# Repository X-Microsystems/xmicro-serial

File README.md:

# XMICRO-SERIAL

[XMICRO](https://github.com/x-microsystems/xmicro-bus) serial communications card providing two RS-232 ports and a PS/2 port.

Datasheet: [XMICRO-SERIAL](Documentation/XMICRO-SERIAL.pdf)

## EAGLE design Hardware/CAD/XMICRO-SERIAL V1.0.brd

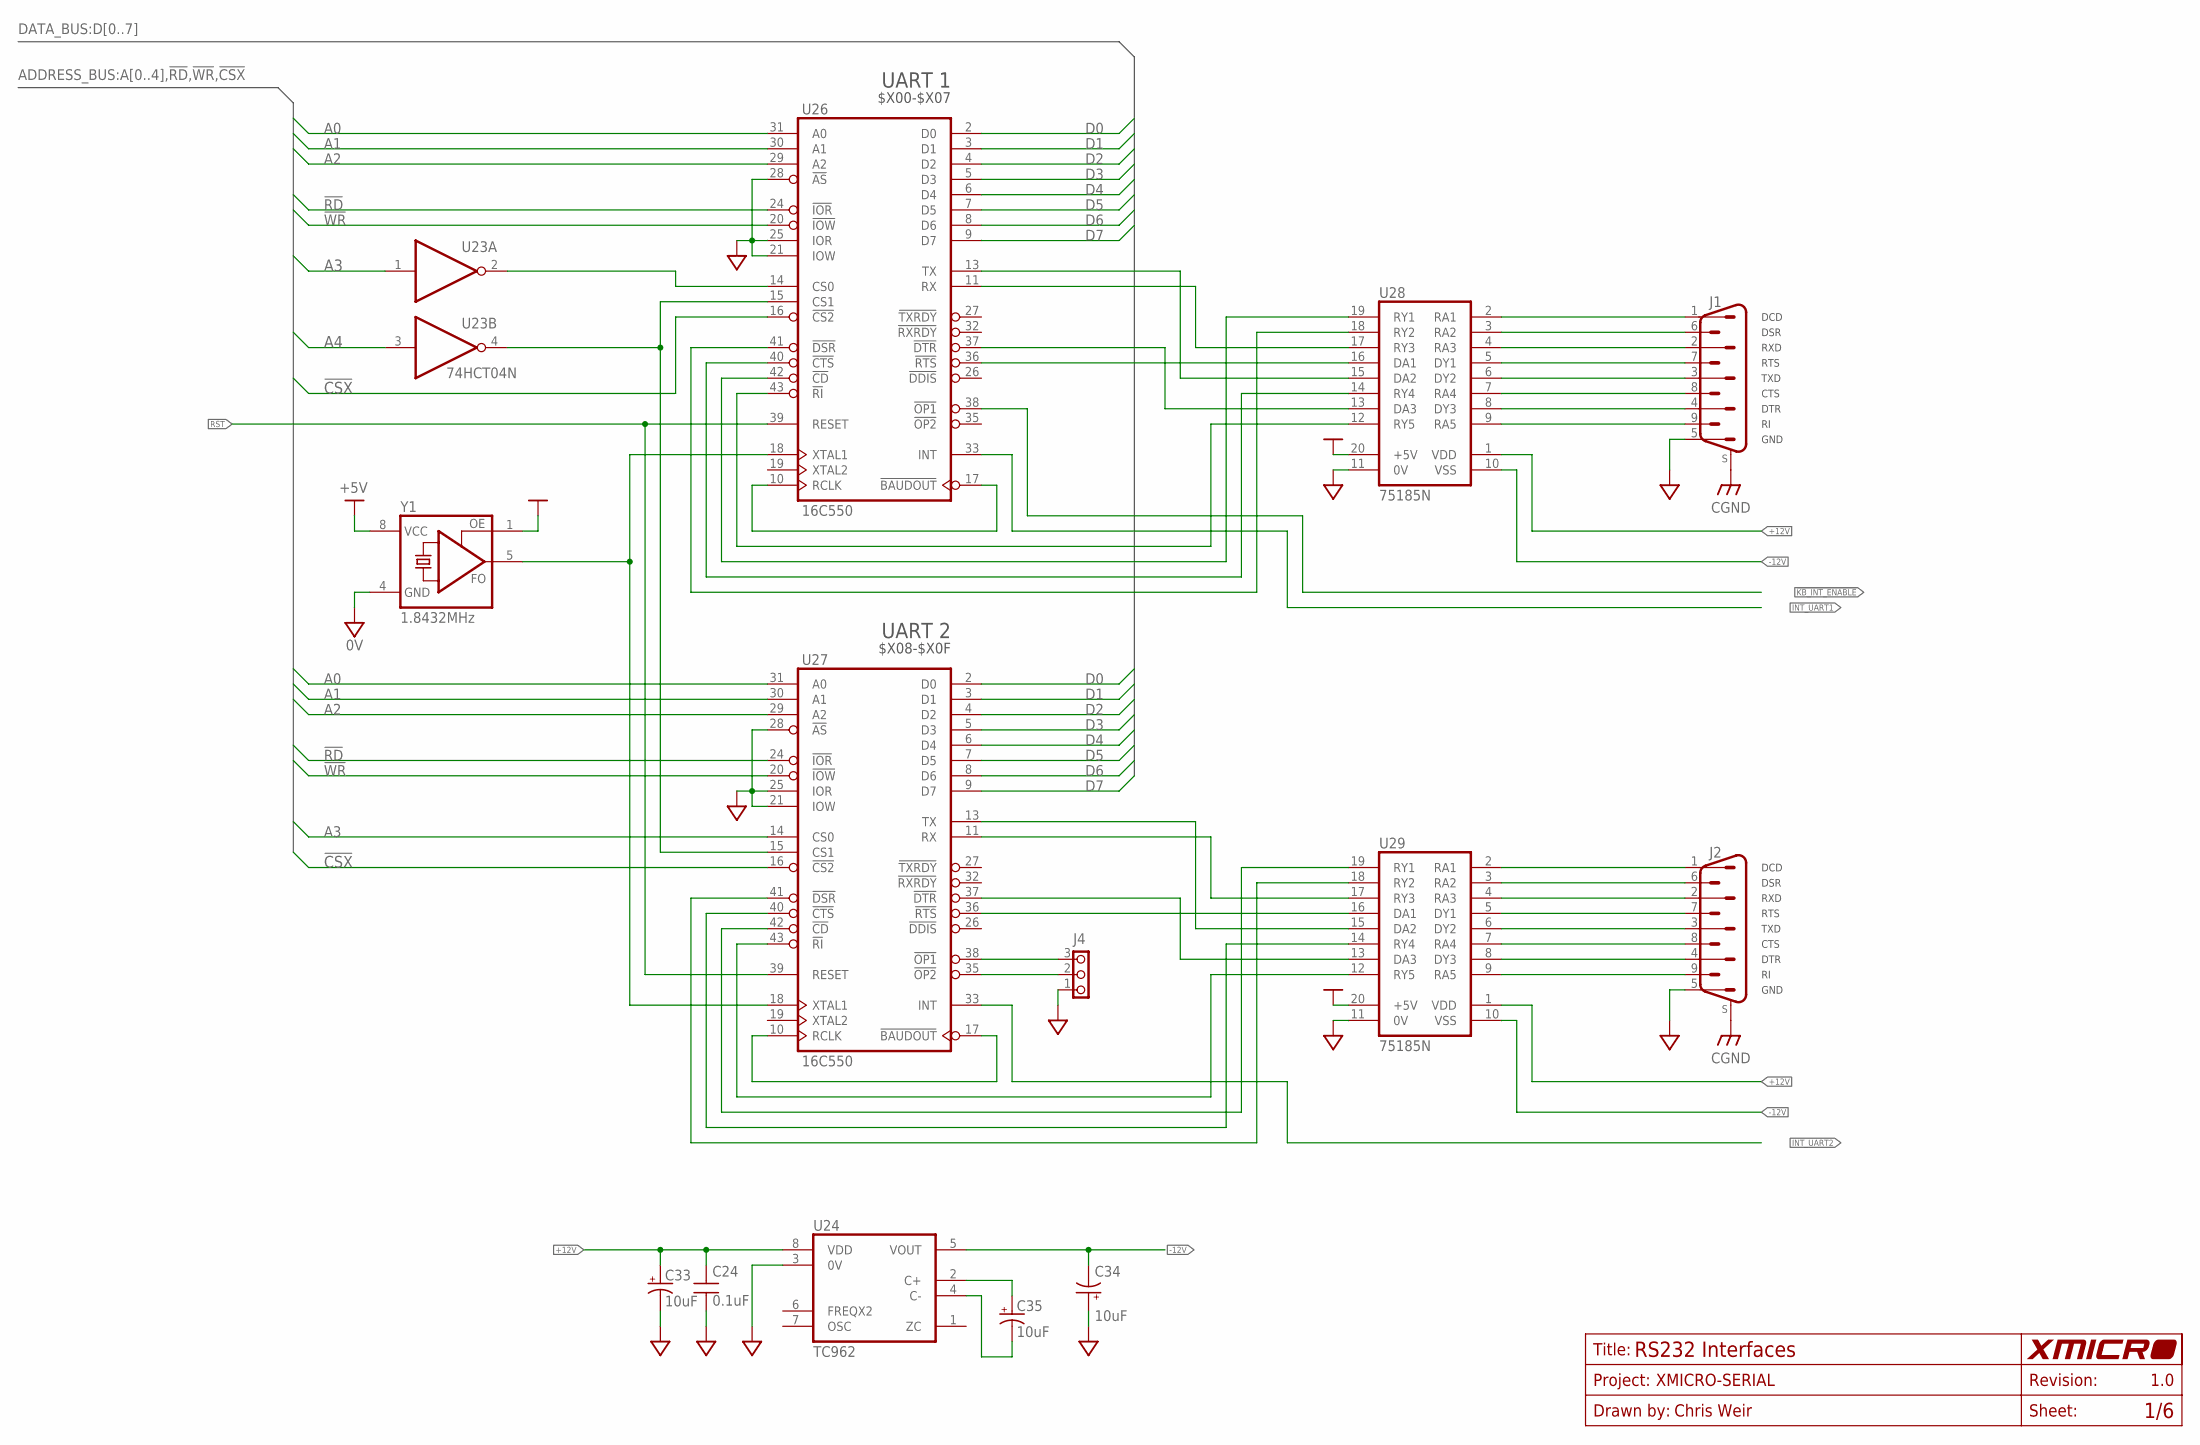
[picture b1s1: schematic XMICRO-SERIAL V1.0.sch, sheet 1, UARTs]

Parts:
C24: 0.1uF; C025-024X044
C33, C34, C35: 10uF; E2,5-5
J1, J2: DSUB-9M-PH; DSUB-9M-H
J4: 1X3
U23: 74HCT04N; DIL14
U24: TC962; DIL8
U26, U27: 16C550; S44
U28, U29: 75185N; DIL20
Y1: 1.8432MHz; DIL08S

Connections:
0V: C24.2, C33.-, C34.+, J1.5, J2.5, J4.1, U23.7 (0V), U24.3 (0V), U26.21 (IOW), U26.22 (0V), U26.25 (IOR), U26.28 (!AS), U27.21 (IOW), U27.22 (0V), U27.25 (IOR), U27.28 (!AS), U28.11 (0V), U29.11 (0V), Y1.4 (0V); also elsewhere on the board
!CSX: U26.16 (!CS2), U27.16 (!CS2); also elsewhere on the board
!KB_INT_ENABLE: U26.38 (!OP1); also elsewhere on the board
!RD: U26.24 (!IOR), U27.24 (!IOR); also elsewhere on the board
!WR: U26.20 (!IOW), U27.20 (!IOW); also elsewhere on the board
+5V: U23.14 (+5V), U26.44 (+5V), U27.44 (+5V), U28.20 (+5V), U29.20 (+5V), Y1.1 (OE), Y1.8 (+5V); also elsewhere on the board
+12V: C24.1, C33.+, U24.8 (VDD), U28.1 (VDD), U29.1 (VDD); also elsewhere on the board
-12V: C34.-, U24.5 (VOUT), U28.10 (VSS), U29.10 (VSS)
A0: U26.31 (A0), U27.31 (A0); also elsewhere on the board
A1: U26.30 (A1), U27.30 (A1); also elsewhere on the board
A2: U26.29 (A2), U27.29 (A2); also elsewhere on the board
A3: U23.1 (I), U27.14 (CS0); also elsewhere on the board
A4: U23.3 (I); also elsewhere on the board
CGND: J1.S1 (S), J1.S2 (S), J2.S1 (S), J2.S2 (S); also elsewhere on the board
D0: U26.2 (D0), U27.2 (D0); also elsewhere on the board
D1: U26.3 (D1), U27.3 (D1); also elsewhere on the board
D2: U26.4 (D2), U27.4 (D2); also elsewhere on the board
D3: U26.5 (D3), U27.5 (D3); also elsewhere on the board
D4: U26.6 (D4), U27.6 (D4); also elsewhere on the board
D5: U26.7 (D5), U27.7 (D5); also elsewhere on the board
D6: U26.8 (D6), U27.8 (D6); also elsewhere on the board
D7: U26.9 (D7), U27.9 (D7); also elsewhere on the board
INT_UART1: U26.33 (INT); also elsewhere on the board
INT_UART2: U27.33 (INT); also elsewhere on the board
unnamed: J1.1, U28.2 (RA1)
unnamed: J1.2, U28.4 (RA3)
unnamed: J1.3, U28.6 (DY2)
unnamed: J1.4, U28.8 (DY3)
unnamed: J1.6, U28.3 (RA2)
unnamed: J1.7, U28.5 (DY1)
unnamed: J1.8, U28.7 (RA4)
unnamed: J1.9, U28.9 (RA5)
unnamed: J2.1, U29.2 (RA1)
unnamed: U26.43 (!RI), U28.12 (RY5)
unnamed: U26.37 (!DTR), U28.13 (DA3)
unnamed: U26.40 (!CTS), U28.14 (RY4)
unnamed: U26.13 (TX), U28.15 (DA2)
unnamed: U26.36 (!RTS), U28.16 (DA1)
unnamed: U26.11 (RX), U28.17 (RY3)
unnamed: U26.41 (!DSR), U28.18 (RY2)
unnamed: U26.42 (!CD), U28.19 (RY1)
unnamed: U26.10 (RCLK), U26.17 (!BAUDOUT)
unnamed: C35.-, U24.4 (C-)
unnamed: J2.2, U29.4 (RA3)
unnamed: J2.3, U29.6 (DY2)
unnamed: J2.4, U29.8 (DY3)
unnamed: J2.6, U29.3 (RA2)
unnamed: J2.7, U29.5 (DY1)
unnamed: J2.8, U29.7 (RA4)
unnamed: J2.9, U29.9 (RA5)
unnamed: C35.+, U24.2 (C+)
unnamed: U23.2 (O), U26.14 (CS0)
unnamed: U27.43 (!RI), U29.12 (RY5)
unnamed: U27.37 (!DTR), U29.13 (DA3)
unnamed: U27.40 (!CTS), U29.14 (RY4)
unnamed: J4.3, U27.38 (!OP1)
unnamed: J4.2, U27.35 (!OP2)
unnamed: U27.13 (TX), U29.15 (DA2)
unnamed: U27.36 (!RTS), U29.16 (DA1)
unnamed: U27.11 (RX), U29.17 (RY3)
unnamed: U27.41 (!DSR), U29.18 (RY2)
unnamed: U27.42 (!CD), U29.19 (RY1)
unnamed: U27.10 (RCLK), U27.17 (!BAUDOUT)
unnamed: U23.4 (O), U26.15 (CS1), U27.15 (CS1)
unnamed: U26.18 (XTAL1), U27.18 (XTAL1), Y1.5 (FO)
RST: U26.39 (RESET), U27.39 (RESET); also elsewhere on the board

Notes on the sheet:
DTR
CTS
TXD
RTS
RXD
DSR
DCD
GND
UART 1
$X00-$X07
UART 2
$X08-$X0F

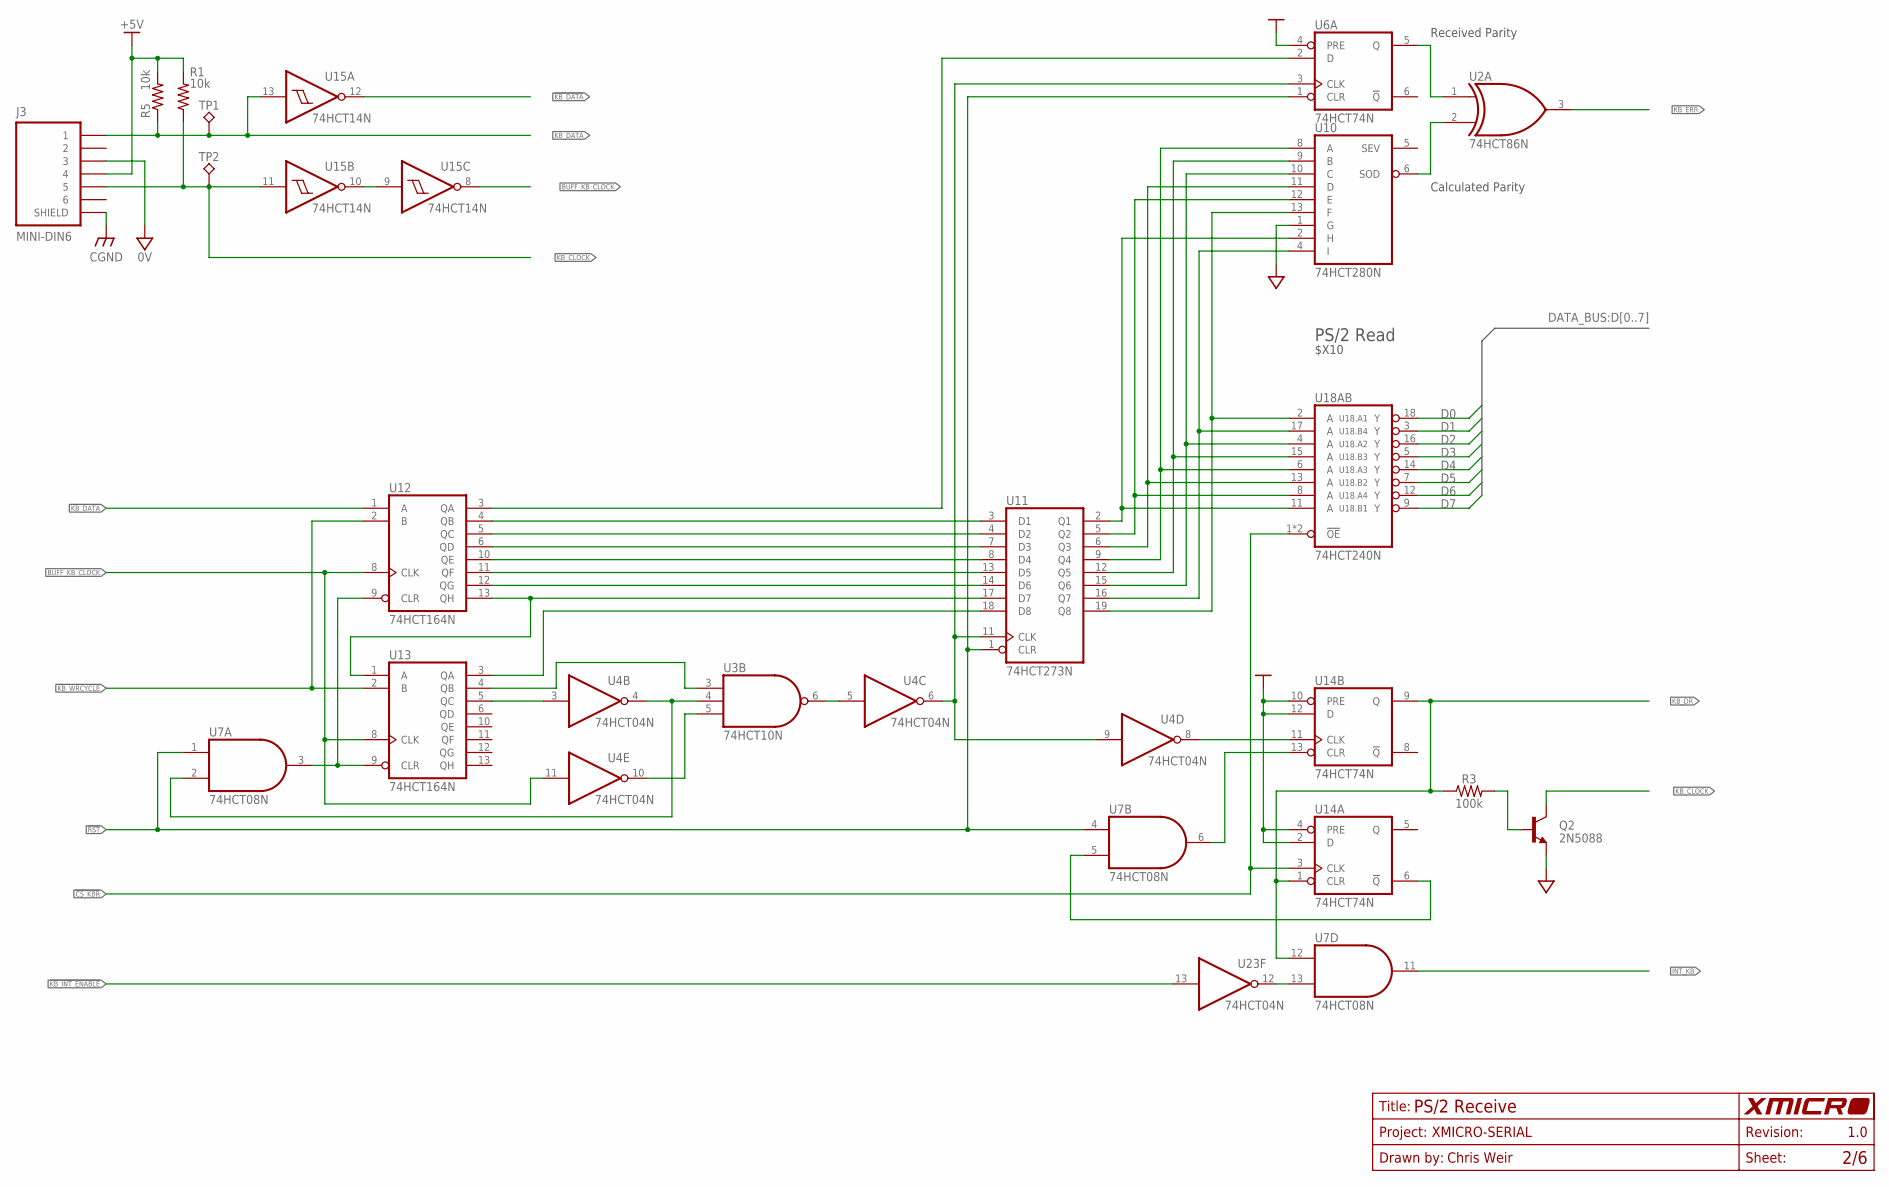
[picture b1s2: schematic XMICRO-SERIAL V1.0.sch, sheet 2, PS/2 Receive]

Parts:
J3: MINI-DIN6
Q2: 2N5088; TO92
R1, R5: 10k; 0207/10
R3: 100k; 0207/10
TP1, TP2: TP-040
U2: 74HCT86N; DIL14
U3: 74HCT10N; DIL14
U4, U23: 74HCT04N; DIL14
U6, U14: 74HCT74N; DIL14
U7: 74HCT08N; DIL14
U10: 74HCT280N; DIL14
U11: 74HCT273N; DIL20
U12, U13: 74HCT164N; DIL14
U15: 74HCT14N; DIL14
U18: 74HCT240N; DIL20

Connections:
0V: J3.3, Q2.1 (E), U2.7 (0V), U3.7 (0V), U4.7 (0V), U6.7 (0V), U7.7 (0V), U10.1 (G), U10.7 (0V), U11.10 (0V), U12.7 (0V), U13.7 (0V), U14.7 (0V), U15.7 (0V), U18.10 (0V), U23.7 (0V); also elsewhere on the board
!CS_KBR: U14.3 (CLK), U18.1 (!OE), U18.19 (!OE); also elsewhere on the board
!KB_DATA: U12.1 (A), U15.12 (O); also elsewhere on the board
!KB_INT_ENABLE: U23.13 (I); also elsewhere on the board
!KB_WRCYCLE: U12.2 (B), U13.2 (B); also elsewhere on the board
!RST: U6.1 (CLR), U7.1 (I0), U7.4 (I0), U11.1 (CLR); also elsewhere on the board
+5V: J3.4, R1.2, R5.2, U2.14 (+5V), U3.14 (+5V), U4.14 (+5V), U6.4 (PRE), U6.14 (+5V), U7.14 (+5V), U10.14 (+5V), U11.20 (+5V), U12.14 (+5V), U13.14 (+5V), U14.2 (D), U14.4 (PRE), U14.10 (PRE), U14.12 (D), U14.14 (+5V), U15.14 (+5V), U18.20 (+5V), U23.14 (+5V); also elsewhere on the board
BUFF_KB_CLOCK: U4.11 (I), U12.8 (CLK), U13.8 (CLK), U15.8 (O); also elsewhere on the board
CGND: J3.G$1 (SHIELD), J3.G$2 (SHIELD), J3.G$3 (SHIELD); also elsewhere on the board
D0: U18.18 (Y); also elsewhere on the board
D1: U18.3 (Y); also elsewhere on the board
D2: U18.16 (Y); also elsewhere on the board
D3: U18.5 (Y); also elsewhere on the board
D4: U18.14 (Y); also elsewhere on the board
D5: U18.7 (Y); also elsewhere on the board
D6: U18.12 (Y); also elsewhere on the board
D7: U18.9 (Y); also elsewhere on the board
INT_KB: U7.11 (O); also elsewhere on the board
KB_CLOCK: J3.5, Q2.3 (C), R1.1, TP2.1, U15.11 (I); also elsewhere on the board
KB_DATA: J3.1, R5.1, TP1.1, U15.13 (I); also elsewhere on the board
KB_DR: R3.1, U7.12 (I0), U14.1 (CLR), U14.9 (Q); also elsewhere on the board
KB_ERR: U2.3 (O); also elsewhere on the board
unnamed: U3.6 (O), U4.5 (I)
unnamed: U4.8 (O), U14.11 (CLK)
unnamed: U15.9 (I), U15.10 (O)
unnamed: U7.13 (I1), U23.12 (O)
unnamed: U11.17 (D7), U12.13 (QH), U13.1 (A)
unnamed: U11.18 (D8), U13.3 (QA)
unnamed: U4.3 (I), U13.5 (QC)
unnamed: U3.4 (I1), U4.4 (O), U7.2 (I1)
unnamed: U4.6 (O), U4.9 (I), U6.3 (CLK), U11.11 (CLK)
unnamed: U3.3 (I0), U13.4 (QB)
unnamed: U11.14 (D6), U12.12 (QG)
unnamed: U11.13 (D5), U12.11 (QF)
unnamed: U11.7 (D3), U12.6 (QD)
unnamed: U11.4 (D2), U12.5 (QC)
unnamed: U11.3 (D1), U12.4 (QB)
unnamed: U6.2 (D), U12.3 (QA)
unnamed: U7.3 (O), U12.9 (CLR), U13.9 (CLR)
unnamed: U7.6 (O), U14.13 (CLR)
unnamed: U2.1 (I0), U6.5 (Q)
unnamed: U10.13 (F), U11.19 (Q8), U18.2 (A)
unnamed: U10.4 (I), U11.16 (Q7), U18.17 (A)
unnamed: U10.10 (C), U11.15 (Q6), U18.4 (A)
unnamed: U10.9 (B), U11.12 (Q5), U18.15 (A)
unnamed: U10.11 (D), U11.6 (Q3), U18.13 (A)
unnamed: U10.12 (E), U11.5 (Q2), U18.8 (A)
unnamed: U10.2 (H), U11.2 (Q1), U18.11 (A)
unnamed: U10.8 (A), U11.9 (Q4), U18.6 (A)
unnamed: U2.2 (I1), U10.6 (SOD)
unnamed: U3.5 (I2), U4.10 (O)
unnamed: Q2.2 (B), R3.2
unnamed: U7.5 (I1), U14.6 (!Q)
UC4: U11.8 (D4), U12.10 (QE)

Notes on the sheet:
Received Parity
Calculated Parity
PS/2 Read
$X10

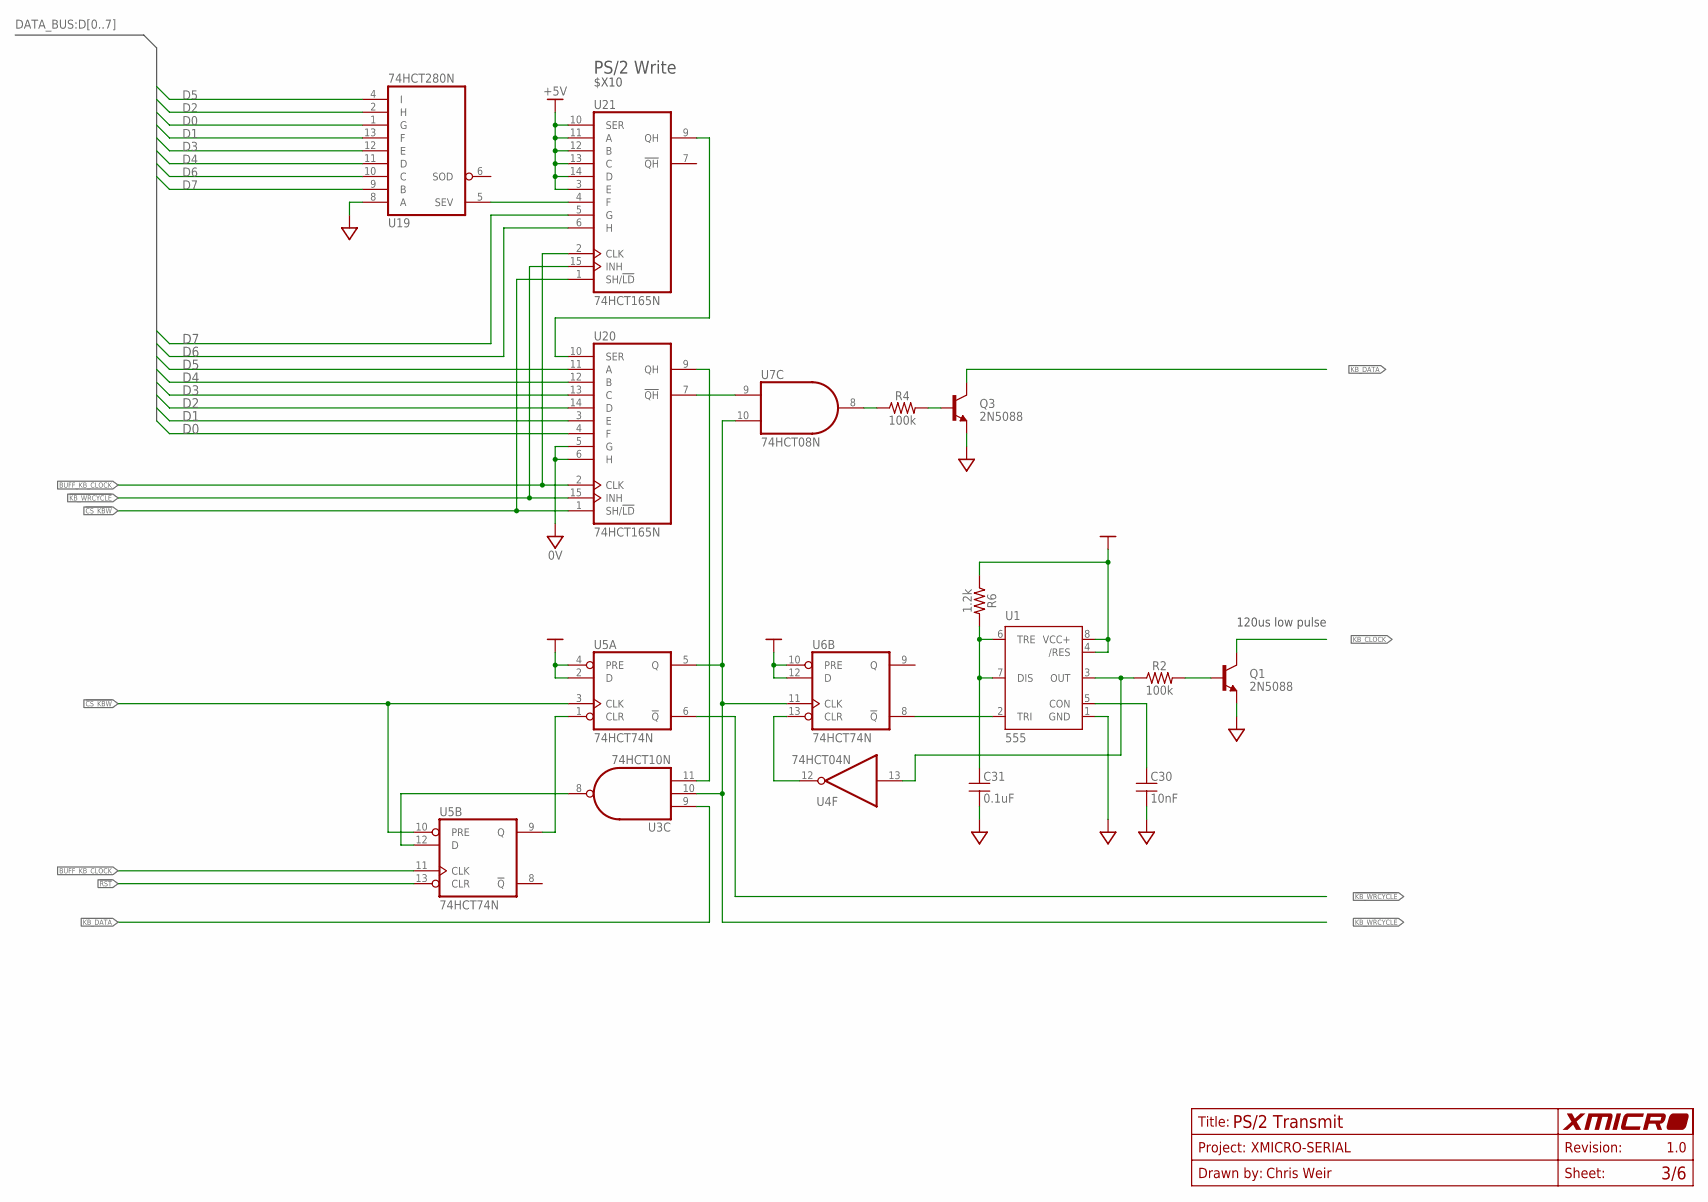
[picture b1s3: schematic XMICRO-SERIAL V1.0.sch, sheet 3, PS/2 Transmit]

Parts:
C30: 10nF; C025-024X044
C31: 0.1uF; C025-024X044
Q1, Q3: 2N5088; TO92
R2, R4: 100k; 0207/10
R6: 1.2k; 0207/10
U1: 555; DIL-08
U3: 74HCT10N; DIL14
U4: 74HCT04N; DIL14
U5, U6: 74HCT74N; DIL14
U7: 74HCT08N; DIL14
U19: 74HCT280N; DIL14
U20, U21: 74HCT165N; DIL16

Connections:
0V: C30.2, C31.2, Q1.1 (E), Q3.1 (E), U1.1 (GND), U3.7 (0V), U4.7 (0V), U5.7 (0V), U6.7 (0V), U7.7 (0V), U19.7 (0V), U19.8 (A), U20.5 (G), U20.6 (H), U20.8 (0V), U21.8 (0V); also elsewhere on the board
!CS_KBW: U5.3 (CLK), U5.10 (PRE), U20.1 (SH/!LD), U21.1 (SH/!LD); also elsewhere on the board
!KB_DATA: U3.9 (I0); also elsewhere on the board
!KB_WRCYCLE: U5.6 (!Q), U20.15 (INH), U21.15 (INH); also elsewhere on the board
!RST: U5.13 (CLR); also elsewhere on the board
+5V: R6.1, U1.4 (/RES), U1.8 (VCC+), U3.14 (+5V), U4.14 (+5V), U5.2 (D), U5.4 (PRE), U5.14 (+5V), U6.10 (PRE), U6.12 (D), U6.14 (+5V), U7.14 (+5V), U19.14 (+5V), U20.16 (+5V), U21.3 (E), U21.10 (SER), U21.11 (A), U21.12 (B), U21.13 (C), U21.14 (D), U21.16 (+5V); also elsewhere on the board
BUFF_KB_CLOCK: U5.11 (CLK), U20.2 (CLK), U21.2 (CLK); also elsewhere on the board
D0: U19.1 (G), U20.4 (F); also elsewhere on the board
D1: U19.13 (F), U20.3 (E); also elsewhere on the board
D2: U19.2 (H), U20.14 (D); also elsewhere on the board
D3: U19.12 (E), U20.13 (C); also elsewhere on the board
D4: U19.11 (D), U20.12 (B); also elsewhere on the board
D5: U19.4 (I), U20.11 (A); also elsewhere on the board
D6: U19.10 (C), U21.6 (H); also elsewhere on the board
D7: U19.9 (B), U21.5 (G); also elsewhere on the board
KB_CLOCK: Q1.3 (C); also elsewhere on the board
KB_DATA: Q3.3 (C); also elsewhere on the board
KB_WRCYCLE: U3.10 (I1), U5.5 (Q), U6.11 (CLK), U7.10 (I1); also elsewhere on the board
unnamed: U3.8 (O), U5.12 (D)
unnamed: U4.12 (O), U6.13 (CLR)
unnamed: U3.11 (I2), U20.9 (QH)
unnamed: U7.9 (I0), U20.7 (!QH)
unnamed: R4.1, U7.8 (O)
unnamed: U20.10 (SER), U21.9 (QH)
unnamed: U19.5 (SEV), U21.4 (F)
unnamed: Q3.2 (B), R4.2
unnamed: Q1.2 (B), R2.2
unnamed: U5.1 (CLR), U5.9 (Q)
unnamed: U1.2 (TRI), U6.8 (!Q)
unnamed: C31.1, R6.2, U1.6 (TRE), U1.7 (DIS)
unnamed: R2.1, U1.3 (OUT), U4.13 (I)
unnamed: C30.1, U1.5 (CON)

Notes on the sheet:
120us low pulse
PS/2 Write
$X10

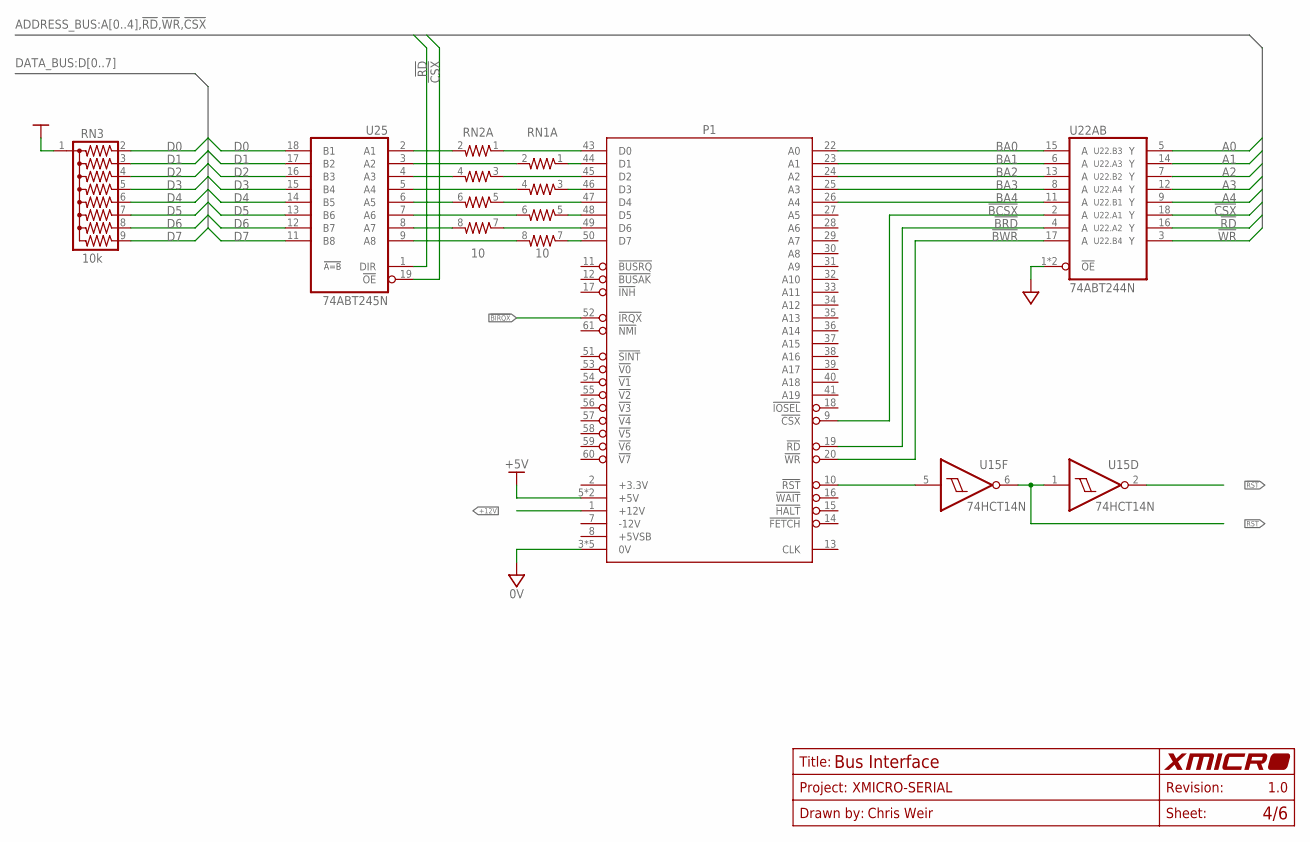
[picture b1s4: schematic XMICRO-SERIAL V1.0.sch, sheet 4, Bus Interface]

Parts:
P1: XMICRO-BUS-EDGE; EDGE62M
RN1, RN2: 10; SIL8
RN3: 10k; SIL9
U15: 74HCT14N; DIL14
U22: 74ABT244N; DIL20
U25: 74ABT245N; DIL20

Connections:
0V: P1.3 (0V), P1.4 (0V), P1.21 (0V), P1.42 (0V), P1.62 (0V), U15.7 (0V), U22.1 (!OE), U22.10 (0V), U22.19 (!OE), U25.10 (0V); also elsewhere on the board
!BCSX: P1.9 (!CSX), U22.2 (A)
!BIRQX: P1.52 (!IRQX); also elsewhere on the board
!BRD: P1.19 (!RD), U22.4 (A)
!BRST: P1.10 (!RST), U15.5 (I)
!BWR: P1.20 (!WR), U22.17 (A)
!CSX: U22.18 (Y), U25.19 (!OE); also elsewhere on the board
!RD: U22.16 (Y), U25.1 (DIR); also elsewhere on the board
!RST: U15.2 (O); also elsewhere on the board
!WR: U22.3 (Y); also elsewhere on the board
+5V: P1.5 (+5V), P1.6 (+5V), RN3.1, U15.14 (+5V), U22.20 (+5V), U25.20 (+5V); also elsewhere on the board
+12V: P1.1 (+12V); also elsewhere on the board
A0: U22.5 (Y); also elsewhere on the board
A1: U22.14 (Y); also elsewhere on the board
A2: U22.7 (Y); also elsewhere on the board
A3: U22.12 (Y); also elsewhere on the board
A4: U22.9 (Y); also elsewhere on the board
BA0: P1.22 (A0), U22.15 (A)
BA1: P1.23 (A1), U22.6 (A)
BA2: P1.24 (A2), U22.13 (A)
BA3: P1.25 (A3), U22.8 (A)
BA4: P1.26 (A4), U22.11 (A)
D0: RN3.2, U25.18 (B1); also elsewhere on the board
D1: RN3.3, U25.17 (B2); also elsewhere on the board
D2: RN3.4, U25.16 (B3); also elsewhere on the board
D3: RN3.5, U25.15 (B4); also elsewhere on the board
D4: RN3.6, U25.14 (B5); also elsewhere on the board
D5: RN3.7, U25.13 (B6); also elsewhere on the board
D6: RN3.8, U25.12 (B7); also elsewhere on the board
D7: RN3.9, U25.11 (B8); also elsewhere on the board
unnamed: RN1.8 (2), U25.9 (A8)
unnamed: P1.49 (D6), RN2.7 (1)
unnamed: RN1.6 (2), U25.7 (A6)
unnamed: P1.47 (D4), RN2.5 (1)
unnamed: RN1.4 (2), U25.5 (A4)
unnamed: P1.45 (D2), RN2.3 (1)
unnamed: RN1.2, U25.3 (A2)
unnamed: P1.43 (D0), RN2.1
unnamed: RN2.2, U25.2 (A1)
unnamed: RN2.4 (2), U25.4 (A3)
unnamed: RN2.6 (2), U25.6 (A5)
unnamed: RN2.8 (2), U25.8 (A7)
unnamed: P1.50 (D7), RN1.7 (1)
unnamed: P1.48 (D5), RN1.5 (1)
unnamed: P1.46 (D3), RN1.3 (1)
unnamed: P1.44 (D1), RN1.1
RST: U15.1 (I), U15.6 (O); also elsewhere on the board

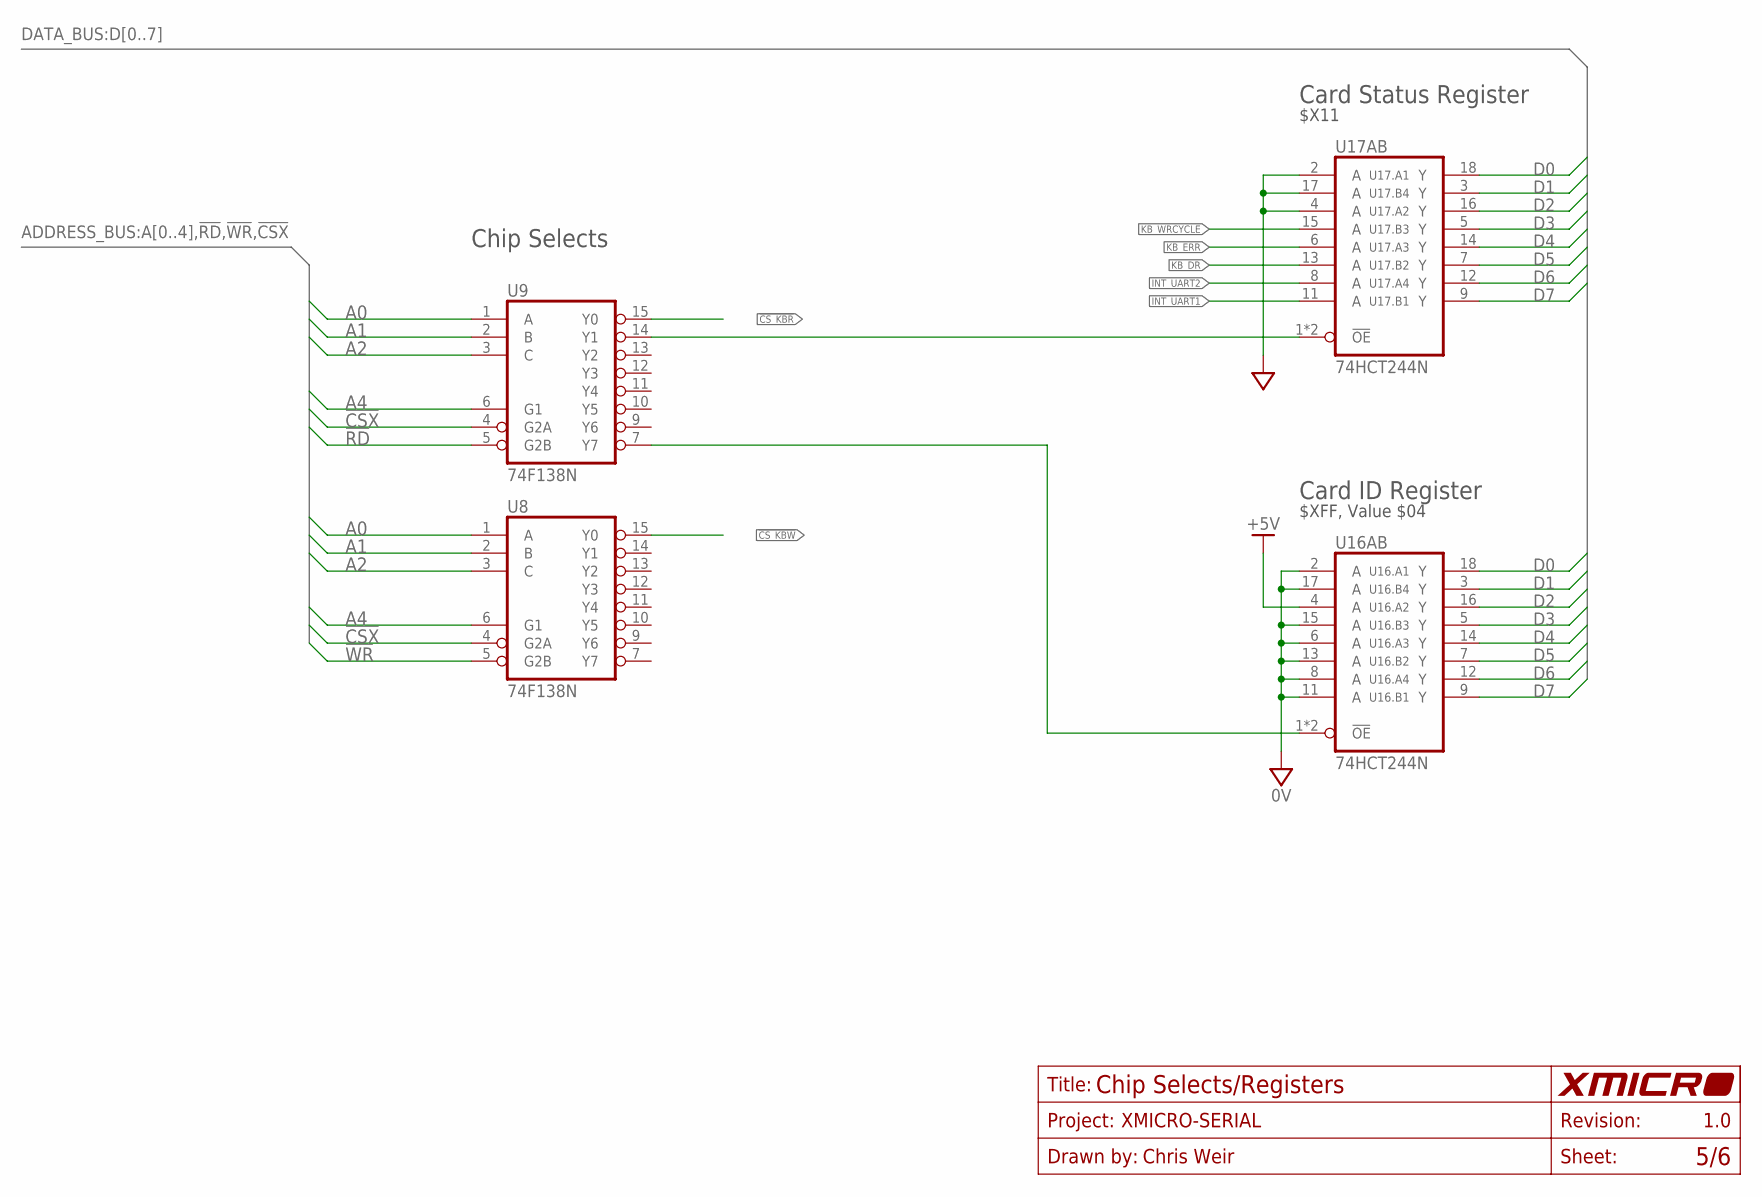
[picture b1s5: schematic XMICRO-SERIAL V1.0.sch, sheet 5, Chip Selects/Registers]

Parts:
U8, U9: 74F138N; DIL16
U16, U17: 74HCT244N; DIL20

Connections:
0V: U8.8 (0V), U9.8 (0V), U16.2 (A), U16.6 (A), U16.8 (A), U16.10 (0V), U16.11 (A), U16.13 (A), U16.15 (A), U16.17 (A), U17.2 (A), U17.4 (A), U17.10 (0V), U17.17 (A); also elsewhere on the board
!CSX: U8.4 (G2A), U9.4 (G2A); also elsewhere on the board
!CS_IDR: U9.7 (Y7), U16.1 (!OE), U16.19 (!OE)
!CS_KBR: U9.15 (Y0); also elsewhere on the board
!CS_KBW: U8.15 (Y0); also elsewhere on the board
!CS_STR: U9.14 (Y1), U17.1 (!OE), U17.19 (!OE)
!RD: U9.5 (G2B); also elsewhere on the board
!WR: U8.5 (G2B); also elsewhere on the board
+5V: U8.16 (+5V), U9.16 (+5V), U16.4 (A), U16.20 (+5V), U17.20 (+5V); also elsewhere on the board
A0: U8.1 (A), U9.1 (A); also elsewhere on the board
A1: U8.2 (B), U9.2 (B); also elsewhere on the board
A2: U8.3 (C), U9.3 (C); also elsewhere on the board
A4: U8.6 (G1), U9.6 (G1); also elsewhere on the board
D0: U16.18 (Y), U17.18 (Y); also elsewhere on the board
D1: U16.3 (Y), U17.3 (Y); also elsewhere on the board
D2: U16.16 (Y), U17.16 (Y); also elsewhere on the board
D3: U16.5 (Y), U17.5 (Y); also elsewhere on the board
D4: U16.14 (Y), U17.14 (Y); also elsewhere on the board
D5: U16.7 (Y), U17.7 (Y); also elsewhere on the board
D6: U16.12 (Y), U17.12 (Y); also elsewhere on the board
D7: U16.9 (Y), U17.9 (Y); also elsewhere on the board
INT_UART1: U17.11 (A); also elsewhere on the board
INT_UART2: U17.8 (A); also elsewhere on the board
KB_DR: U17.13 (A); also elsewhere on the board
KB_ERR: U17.6 (A); also elsewhere on the board
KB_WRCYCLE: U17.15 (A); also elsewhere on the board

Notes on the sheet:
Card ID Register
$XFF, Value $04
Chip Selects
Card Status Register
$X11

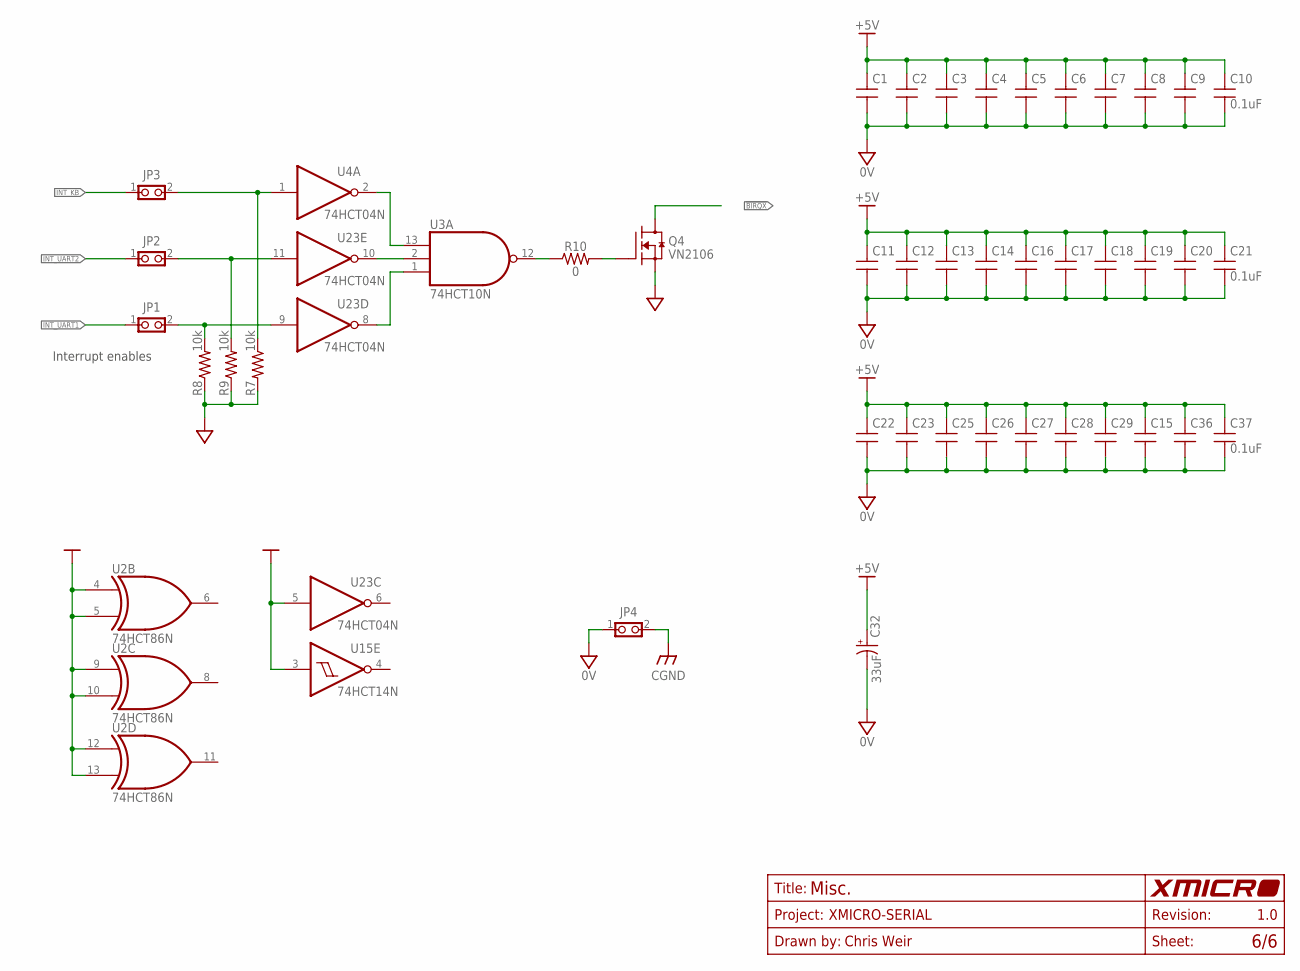
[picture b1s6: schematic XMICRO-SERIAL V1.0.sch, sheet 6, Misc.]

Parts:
C1, C2, C3, C4, C5, C6, C7, C8, C9, C10, C11, C12, C13, C14, C15, C16, C17, C18, C19, C20, C21, C22, C23, C25, C26, C27, C28, C29, C36, C37: 0.1uF; C025-024X044
C32: 33uF; E2,5-6
JP1, JP2, JP3, JP4: 1X2-THRU; 1X2
Q4: VN2106; TO92
R7, R8, R9: 10k; 0207/10
R10: 0; 0207/10
U2: 74HCT86N; DIL14
U3: 74HCT10N; DIL14
U4, U23: 74HCT04N; DIL14
U15: 74HCT14N; DIL14

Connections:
0V: C1.2, C2.2, C3.2, C4.2, C5.2, C6.2, C7.2, C8.2, C9.2, C10.2, C11.2, C12.2, C13.2, C14.2, C15.2, C16.2, C17.2, C18.2, C19.2, C20.2, C21.2, C22.2, C23.2, C25.2, C26.2, C27.2, C28.2, C29.2, C32.-, C36.2, C37.2, JP4.1, Q4.1 (S), R7.2, R8.1, R9.1, U2.7 (0V), U3.7 (0V), U4.7 (0V), U15.7 (0V), U23.7 (0V); also elsewhere on the board
!BIRQX: Q4.3 (D); also elsewhere on the board
+5V: C1.1, C2.1, C3.1, C4.1, C5.1, C6.1, C7.1, C8.1, C9.1, C10.1, C11.1, C12.1, C13.1, C14.1, C15.1, C16.1, C17.1, C18.1, C19.1, C20.1, C21.1, C22.1, C23.1, C25.1, C26.1, C27.1, C28.1, C29.1, C32.+, C36.1, C37.1, U2.4 (I0), U2.5 (I1), U2.9 (I0), U2.10 (I1), U2.12 (I0), U2.13 (I1), U2.14 (+5V), U3.14 (+5V), U4.14 (+5V), U15.3 (I), U15.14 (+5V), U23.5 (I), U23.14 (+5V); also elsewhere on the board
CGND: JP4.2; also elsewhere on the board
INT_KB: JP3.1; also elsewhere on the board
INT_UART1: JP1.1; also elsewhere on the board
INT_UART2: JP2.1; also elsewhere on the board
unnamed: R10.1, U3.12 (O)
unnamed: JP3.2, R7.1, U4.1 (I)
unnamed: U3.1 (I0), U23.8 (O)
unnamed: Q4.2 (G), R10.2
unnamed: U3.13 (I2), U4.2 (O)
unnamed: U3.2 (I1), U23.10 (O)
unnamed: JP1.2, R8.2, U23.9 (I)
unnamed: JP2.2, R9.2, U23.11 (I)

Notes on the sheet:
Interrupt enables

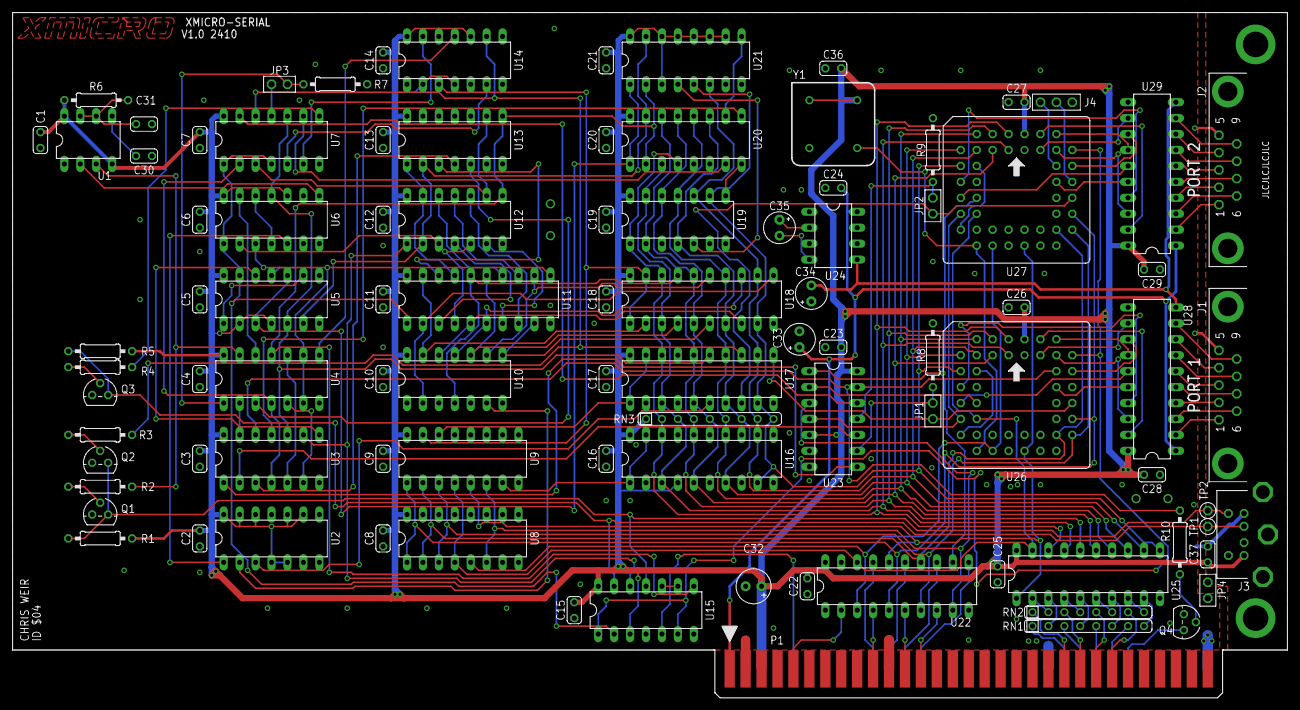
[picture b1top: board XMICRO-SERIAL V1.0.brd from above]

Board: 2 copper layers, 203.2 x 109.2 mm, 95 parts (0 on the bottom side), 160 nets.
